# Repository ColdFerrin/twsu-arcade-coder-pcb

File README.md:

# twsu-arcade-coder-pcb

An open source repository for replicating the board schematics and layout of Tech Will Save Us's ESP32-powered Arcade Coder RGB input matrix.

This project is viewable in KiCad 9.0+

I am not an electrical engineer, this is my best guess at replicating the schematics and layout of the board.  

## Community

Following [a very generous sharing of dozens of Arcade Coders](https://www.reddit.com/r/LinusTechTips/comments/1jgk9cr/how_can_i_stop_all_of_this_from_becoming_ewaste/), there is now a community of developers working on developing software for this board on [Discord](https://discord.gg/QWCUWKAqts) (if this URL does not work please message someone in the reddit thread who has joined).
If you join the community please make an effort to share your discoveries in a public space for future preservation.

## How it works

- 9 daisy chained HC595 chips are daisy-chained and used to control 24 RGB LEDs (two of the twelve rows) from 3 ESP32 pins
- 6 multiplexing channels are used to control the rows which the HC595s are in control of, this is done with an IC2012 (LS138) which requires 3 pins; the other 2 channels uses are unknown
- buttons on matrix are partially handled by 6 GPIO pins which are grouped in correspondence with the multiplexed LED channels (seemingly also partially handled by values being distorted by red LEDs)
- 2 status LEDs on the rear of the device are directly controlled by a GPIO pin each, as is the home button on the side
- accelerometer which I have not tested

### Pinout

HC595:
- Data: GPIO5
- Clock: GPIO17
- Latch: GPIO16
- OE: GPIO4 

ICN2012 (LS138, controls multiplexing to allow control of all 144 RGB LEDs):
- A0: GPIO19
- A1: GPIO18
- A2: GPIO21
- E1: 3.3v
- E2: GND (after a chain of resistors)

Button inputs (tracks if any button in row is pressed):
- 6 and 12: GPIO32
- 5 and 11: GPIO33
- 4 and 10: GPIO34
- 3 and 9: GPIO35
- 2 and 8: GPIO36
- 1 and 7: GPIO39

Other:
- LED1: GPIO22
- LED2: GPIO23
- Home: GPIO2 (seems unreliable)
- Motion sensor: GPIO27/GPIO26 for possible accelerometer in middle of board

Note: Usage of GPIO4 may impact ability to use Wifi from what I can see, will need to verify and see if it can be worked around.

## Errata

The project is currently schematics only, and currently only has the LED matrix and logic chips. I am working on figuring out the wiring of the button matrix, but that is more complicated as it uses some kind of resister ladder.

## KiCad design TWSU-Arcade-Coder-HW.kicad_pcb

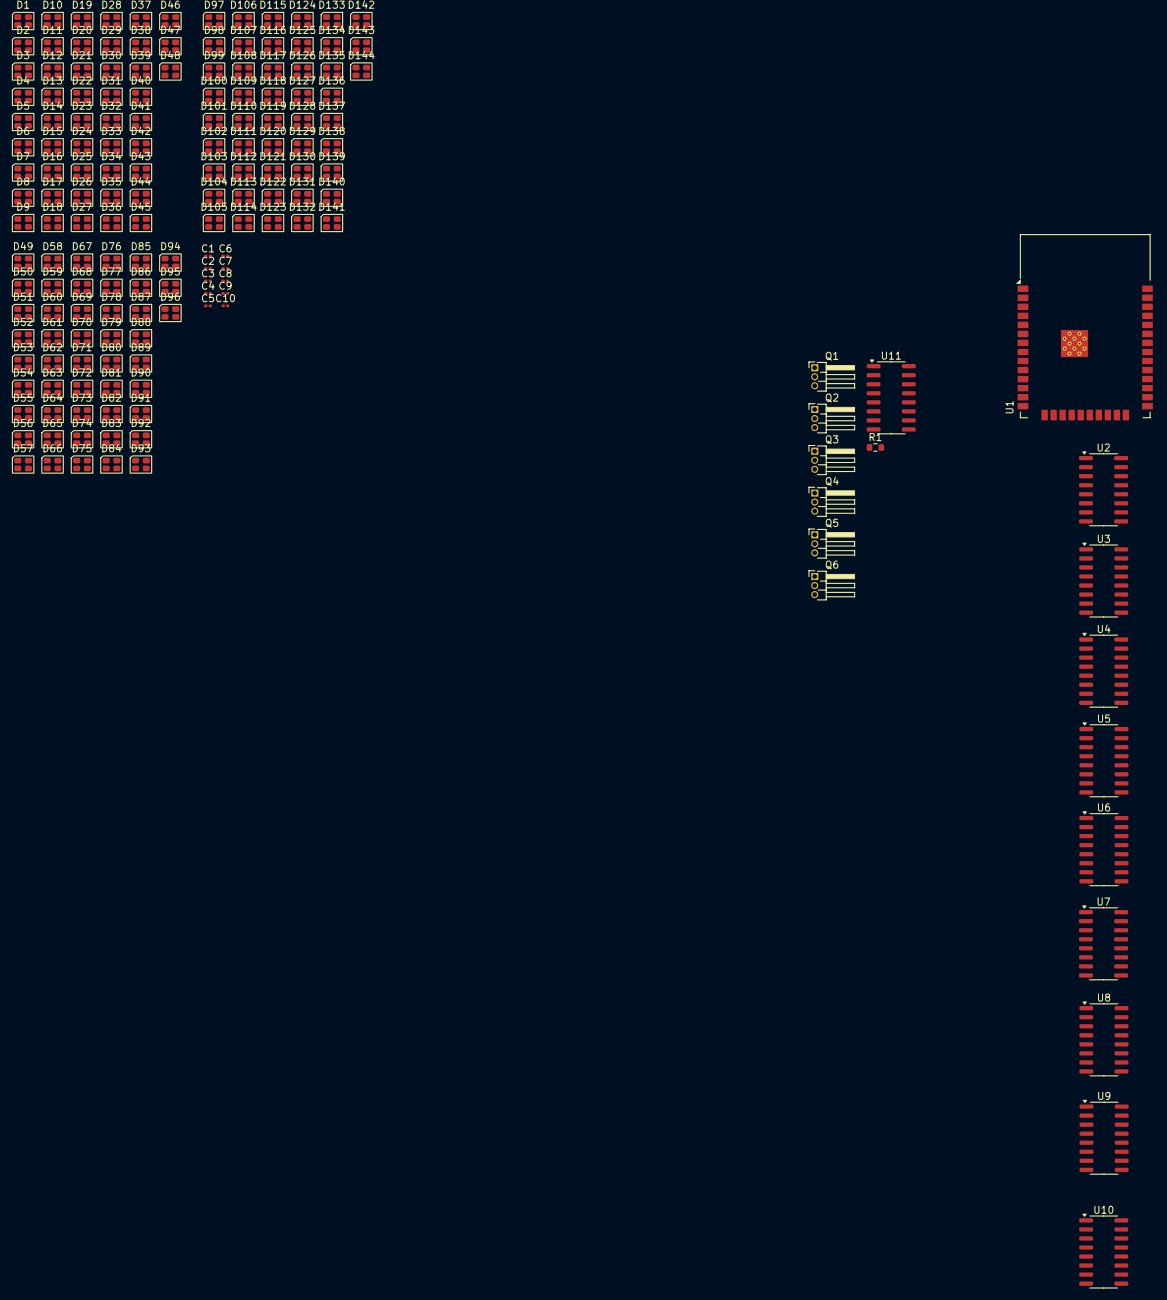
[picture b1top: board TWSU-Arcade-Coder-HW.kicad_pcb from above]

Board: 2 copper layers, 172 parts (0 on the bottom side), 65 nets, no tracks yet.

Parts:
C1, C2, C3, C4, C5, C6, C7, C8, C9, C10: C; C_0201_0603Metric
D1, D2, D3, D4, D5, D6, D7, D8, D9, D10, D11, D12, D13, D14, D15, D16, D17, D18, D19, D20, D21, D22, D23, D24, D25, D26, D27, D28, D29, D30, D31, D32, D33, D34, D35, D36, D37, D38, D39, D40, D41, D42, D43, D44, D45, D46, D47, D48, D49, D50, D51, D52, D53, D54, D55, D56, D57, D58, D59, D60, D61, D62, D63, D64, D65, D66, D67, D68, D69, D70, D71, D72, D73, D74, D75, D76, D77, D78, D79, D80, D81, D82, D83, D84, D85, D86, D87, D88, D89, D90, D91, D92, D93, D94, D95, D96, D97, D98, D99, D100, D101, D102, D103, D104, D105, D106, D107, D108, D109, D110, D111, D112, D113, D114, D115, D116, D117, D118, D119, D120, D121, D122, D123, D124, D125, D126, D127, D128, D129, D130, D131, D132, D133, D134, D135, D136, D137, D138, D139, D140, D141, D142, D143, D144: LED_ARGB; LED_Cree-PLCC4_2x2mm_CW
Q1, Q2, Q3, Q4, Q5, Q6: PMOS; PinHeader_1x03_P1.27mm_Horizontal
R1: R; R_0603_1608Metric
U1: ESP32-WROOM-32D
U2, U3, U4, U5, U6, U7, U8, U9, U10: 74HC595; SOIC-16_3.9x9.9mm_P1.27mm
U11: SOIC-16_3.9x9.9mm_P1.27mm

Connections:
+3.3V: U1.2 (VDD), U2.16 (VCC), U3.16 (VCC), U4.16 (VCC), U5.16 (VCC), U6.16 (VCC), U7.16 (VCC), U8.16 (VCC), U9.16 (VCC), U10.16 (VCC)
+5V: Q1.1 (D), Q2.1 (D), Q3.1 (D), Q4.1 (D), Q5.1 (D), Q6.1 (D), U11.1 (VCC), U11.9 (VCC)
/595 Data: U1.29 (IO5), U2.14 (SER)
/595 OE: U1.26 (IO4), U2.13 (~OE), U3.13 (~OE), U4.13 (~OE), U5.13 (~OE), U6.13 (~OE), U7.13 (~OE), U8.13 (~OE), U9.13 (~OE), U10.13 (~OE)
/595 R CLK: U1.27 (IO16), U2.12 (RCLK), U3.12 (RCLK), U4.12 (RCLK), U5.12 (RCLK), U6.12 (RCLK), U7.12 (RCLK), U8.12 (RCLK), U9.12 (RCLK), U10.12 (RCLK)
/595 SR CLK: R1.1, U2.11 (SRCLK), U3.11 (SRCLK), U4.11 (SRCLK), U5.11 (SRCLK), U6.11 (SRCLK), U7.11 (SRCLK), U8.11 (SRCLK), U9.11 (SRCLK), U10.11 (SRCLK)
/Col addr 0: U1.31 (IO19), U11.15 (A0)
/Col addr 1: U1.30 (IO18), U11.16 (A1)
/Col addr 2: U1.33 (IO21), U11.2 (A2)
GND: C1.2, C2.1, C3.1, C4.1, C5.1, C6.1, C7.1, C8.1, C9.1, C10.1, U1.1 (GND), U1.15 (GND), U1.38 (GND), U1.39 (GND), U2.8 (GND), U3.8 (GND), U4.8 (GND), U5.8 (GND), U6.8 (GND), U7.8 (GND), U8.8 (GND), U9.8 (GND), U10.8 (GND), U11.8 (GND)
unnamed: C1.1, R1.2, U1.28 (IO17)
unnamed: U2.9 (QH'), U3.14 (SER)
unnamed: C2.2, U2.10 (~SRCLR)
unnamed: U3.9 (QH'), U4.14 (SER)
unnamed: C3.2, U3.10 (~SRCLR)
unnamed: U4.9 (QH'), U5.14 (SER)
unnamed: C4.2, U4.10 (~SRCLR)
unnamed: U5.9 (QH'), U6.14 (SER)
unnamed: C5.2, U5.10 (~SRCLR)
unnamed: U6.9 (QH'), U7.14 (SER)
unnamed: C9.2, U6.10 (~SRCLR)
unnamed: U7.9 (QH'), U8.14 (SER)
unnamed: C8.2, U7.10 (~SRCLR)
unnamed: U8.9 (QH'), U9.14 (SER)
unnamed: C7.2, U8.10 (~SRCLR)
unnamed: C6.2, U9.10 (~SRCLR)
unnamed: U9.9 (QH'), U10.14 (SER)
unnamed: C10.2, U10.10 (~SRCLR)
RS1: D1.1 (A), D2.1 (A), D3.1 (A), D4.1 (A), D5.1 (A), D6.1 (A), D7.1 (A), D8.1 (A), D9.1 (A), D10.1 (A), D11.1 (A), D12.1 (A), D51.1 (A), D55.1 (A), D59.1 (A), D63.1 (A), D67.1 (A), D71.1 (A), D75.1 (A), D79.1 (A), D83.1 (A), D87.1 (A), D91.1 (A), D95.1 (A), U11.5 (OUT_2)
RS2: D13.1 (A), D14.1 (A), D15.1 (A), D16.1 (A), D17.1 (A), D18.1 (A), D19.1 (A), D20.1 (A), D21.1 (A), D22.1 (A), D23.1 (A), D24.1 (A), D52.1 (A), D56.1 (A), D60.1 (A), D64.1 (A), D68.1 (A), D72.1 (A), D76.1 (A), D80.1 (A), D84.1 (A), D88.1 (A), D92.1 (A), D96.1 (A), U11.6 (OUT_3)
RS3: D25.1 (A), D26.1 (A), D27.1 (A), D28.1 (A), D29.1 (A), D30.1 (A), D31.1 (A), D32.1 (A), D33.1 (A), D34.1 (A), D35.1 (A), D36.1 (A), D97.1 (A), D101.1 (A), D105.1 (A), D109.1 (A), D113.1 (A), D117.1 (A), D121.1 (A), D125.1 (A), D129.1 (A), D133.1 (A), D137.1 (A), D141.1 (A), U11.12 (OUT_5)
RS4: D37.1 (A), D38.1 (A), D39.1 (A), D40.1 (A), D41.1 (A), D42.1 (A), D43.1 (A), D44.1 (A), D45.1 (A), D46.1 (A), D47.1 (A), D48.1 (A), D98.1 (A), D102.1 (A), D106.1 (A), D110.1 (A), D114.1 (A), D118.1 (A), D122.1 (A), D126.1 (A), D130.1 (A), D134.1 (A), D138.1 (A), D142.1 (A), U11.11 (OUT_4)
RS5: D49.1 (A), D53.1 (A), D57.1 (A), D61.1 (A), D65.1 (A), D69.1 (A), D73.1 (A), D77.1 (A), D81.1 (A), D85.1 (A), D89.1 (A), D93.1 (A), D99.1 (A), D103.1 (A), D107.1 (A), D111.1 (A), D115.1 (A), D119.1 (A), D123.1 (A), D127.1 (A), D131.1 (A), D135.1 (A), D139.1 (A), D143.1 (A), U11.4 (OUT_1)
RS6: D50.1 (A), D54.1 (A), D58.1 (A), D62.1 (A), D66.1 (A), D70.1 (A), D74.1 (A), D78.1 (A), D82.1 (A), D86.1 (A), D90.1 (A), D94.1 (A), D100.1 (A), D104.1 (A), D108.1 (A), D112.1 (A), D116.1 (A), D120.1 (A), D124.1 (A), D128.1 (A), D132.1 (A), D136.1 (A), D140.1 (A), D144.1 (A), U11.13 (OUT_6)
s1b1: D12.4 (BK), D24.4 (BK), D36.4 (BK), D48.4 (BK), D93.4 (BK), D94.4 (BK), U8.15 (QA)
s1b2: D11.4 (BK), D23.4 (BK), D35.4 (BK), D47.4 (BK), D89.4 (BK), D90.4 (BK), U8.1 (QB)
s1b3: D10.4 (BK), D22.4 (BK), D34.4 (BK), D46.4 (BK), D85.4 (BK), D86.4 (BK), U8.2 (QC)
s1b4: D9.4 (BK), D21.4 (BK), D33.4 (BK), D45.4 (BK), D81.4 (BK), D82.4 (BK), U8.3 (QD)
s1b5: D8.4 (BK), D20.4 (BK), D32.4 (BK), D44.4 (BK), D77.4 (BK), D78.4 (BK), U8.4 (QE)
s1b6: D7.4 (BK), D19.4 (BK), D31.4 (BK), D43.4 (BK), D73.4 (BK), D74.4 (BK), U8.5 (QF)
s1b7: D6.4 (BK), D18.4 (BK), D30.4 (BK), D42.4 (BK), D69.4 (BK), D70.4 (BK), U8.6 (QG)
s1b8: D5.4 (BK), D17.4 (BK), D29.4 (BK), D41.4 (BK), D65.4 (BK), D66.4 (BK), U8.7 (QH)
s1g1: D12.3 (GK), D24.3 (GK), D36.3 (GK), D48.3 (GK), D93.3 (GK), D94.3 (GK), U10.15 (QA)
s1g2: D11.3 (GK), D23.3 (GK), D35.3 (GK), D47.3 (GK), D89.3 (GK), D90.3 (GK), U10.1 (QB)
s1g3: D10.3 (GK), D22.3 (GK), D34.3 (GK), D46.3 (GK), D85.3 (GK), D86.3 (GK), U10.2 (QC)
s1g4: D9.3 (GK), D21.3 (GK), D33.3 (GK), D45.3 (GK), D81.3 (GK), D82.3 (GK), U10.3 (QD)
s1g5: D8.3 (GK), D20.3 (GK), D32.3 (GK), D44.3 (GK), D77.3 (GK), D78.3 (GK), U10.4 (QE)
s1g6: D7.3 (GK), D19.3 (GK), D31.3 (GK), D43.3 (GK), D73.3 (GK), D74.3 (GK), U10.5 (QF)
s1g7: D6.3 (GK), D18.3 (GK), D30.3 (GK), D42.3 (GK), D69.3 (GK), D70.3 (GK), U10.6 (QG)
s1g8: D5.3 (GK), D17.3 (GK), D29.3 (GK), D41.3 (GK), D65.3 (GK), D66.3 (GK), U10.7 (QH)
s1r1: D12.2 (RK), D24.2 (RK), D36.2 (RK), D48.2 (RK), D93.2 (RK), D94.2 (RK), U9.15 (QA)
s1r2: D11.2 (RK), D23.2 (RK), D35.2 (RK), D47.2 (RK), D89.2 (RK), D90.2 (RK), U9.1 (QB)
s1r3: D10.2 (RK), D22.2 (RK), D34.2 (RK), D46.2 (RK), D85.2 (RK), D86.2 (RK), U9.2 (QC)
s1r4: D9.2 (RK), D21.2 (RK), D33.2 (RK), D45.2 (RK), D81.2 (RK), D82.2 (RK), U9.3 (QD)
s1r5: D8.2 (RK), D20.2 (RK), D32.2 (RK), D44.2 (RK), D77.2 (RK), D78.2 (RK), U9.4 (QE)
s1r6: D7.2 (RK), D19.2 (RK), D31.2 (RK), D43.2 (RK), D73.2 (RK), D74.2 (RK), U9.5 (QF)
s1r7: D6.2 (RK), D18.2 (RK), D30.2 (RK), D42.2 (RK), D69.2 (RK), D70.2 (RK), U9.6 (QG)
s1r8: D5.2 (RK), D17.2 (RK), D29.2 (RK), D41.2 (RK), D65.2 (RK), D66.2 (RK), U9.7 (QH)
s2b1: D4.4 (BK), D16.4 (BK), D28.4 (BK), D40.4 (BK), D61.4 (BK), D62.4 (BK), U5.15 (QA)
s2g1: D4.3 (GK), D16.3 (GK), D28.3 (GK), D40.3 (GK), D61.3 (GK), D62.3 (GK), U7.15 (QA)
s2r1: D4.2 (RK), D16.2 (RK), D28.2 (RK), D40.2 (RK), D61.2 (RK), D62.2 (RK), U6.15 (QA)
s2r2: D3.2 (RK), D15.2 (RK), D27.2 (RK), D39.2 (RK), D57.2 (RK), D58.2 (RK), U6.1 (QB)
s2r3: D2.2 (RK), D14.2 (RK), D26.2 (RK), D38.2 (RK), D53.2 (RK), D54.2 (RK), U6.2 (QC)
s2r4: D1.2 (RK), D13.2 (RK), D25.2 (RK), D37.2 (RK), D49.2 (RK), D50.2 (RK), U6.3 (QD)
s2r5: D63.2 (RK), D64.2 (RK), D109.2 (RK), D110.2 (RK), D111.2 (RK), D112.2 (RK), U6.4 (QE)

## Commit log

2025-04-23 Add initial schematic files
